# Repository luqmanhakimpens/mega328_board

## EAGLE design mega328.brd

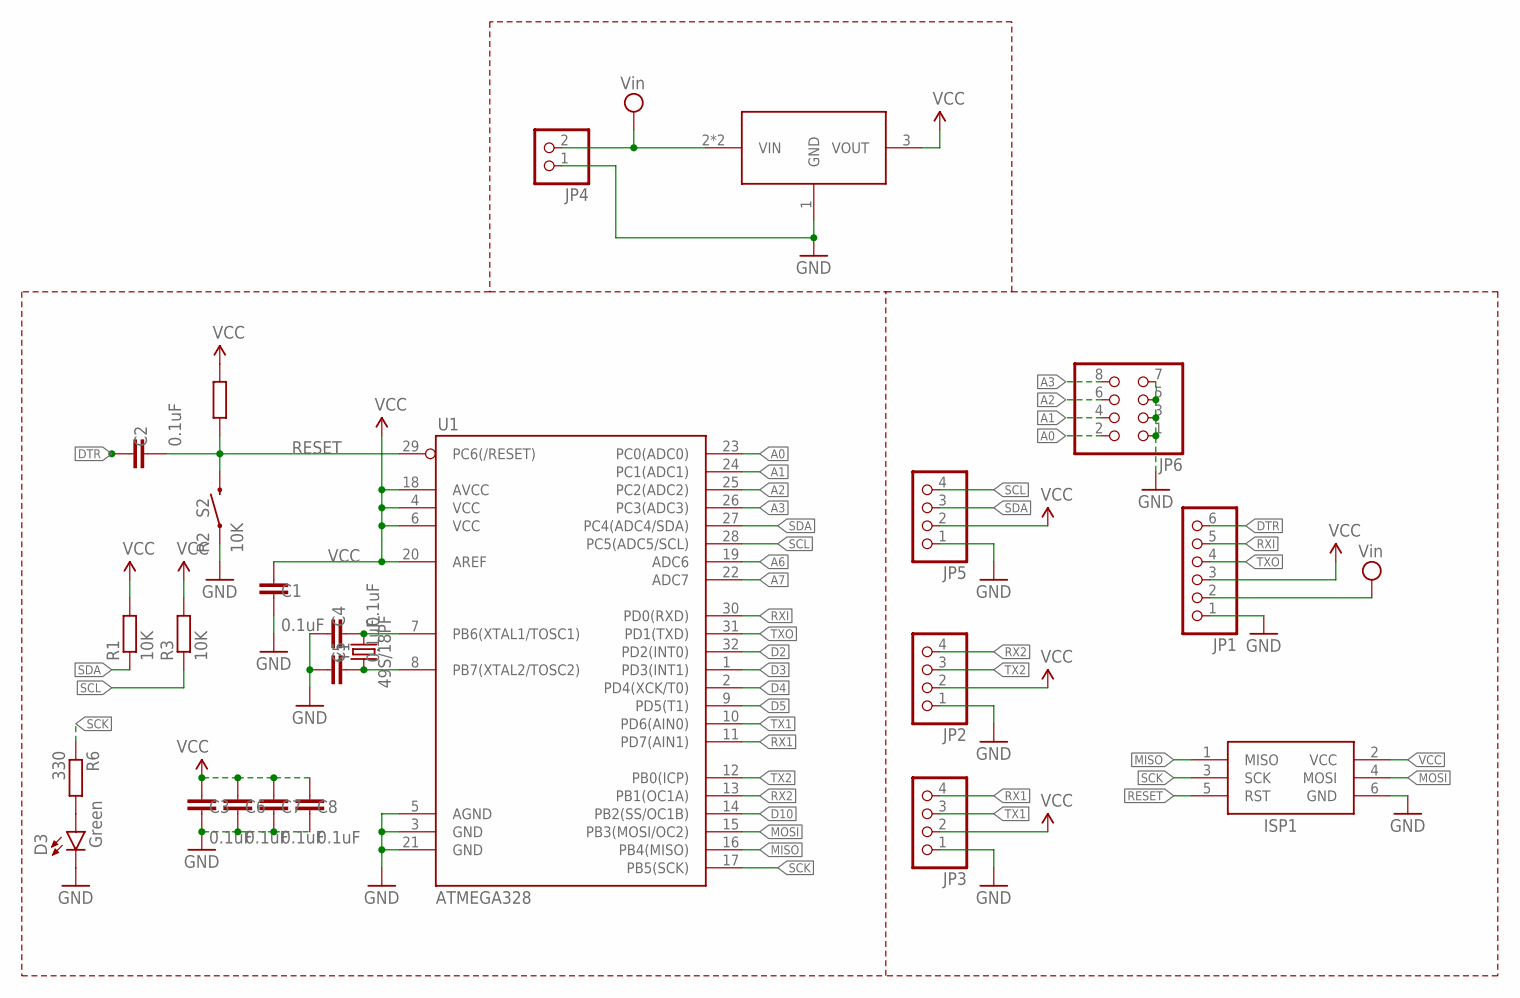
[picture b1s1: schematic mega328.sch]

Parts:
C1, C2, C3, C4, C5, C6, C7, C8: 0.1uF; C0805
D3: Green; CHIP-LED0805
ISP1: AVRISP3D; 2X03
JP1: PINHD-1X06_2.54-S; 1X06
JP2, JP3, JP5: PINHD-1X04_2.54-S; 1X04-S
JP4: PINHD-1X02_2.54-S; 1X02-S
JP6: PINHD-2X4; 2X04
R1, R2, R3: 10K; R0805
R6: 330; R0805
S2: MOMENTARY-SWITCH-SPST-PTH-6.0MM; TACTILE_SWITCH_PTH_6.0MM
U1: ATMEGA328; TQFP32-08
U$1: AIC1722A-33PXATR; SOT89
Y1: 49S/18PF; XTAL_HC49

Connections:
A0: JP6.2, U1.23 (PC0(ADC0))
A1: JP6.4, U1.24 (PC1(ADC1))
A2: JP6.6, U1.25 (PC2(ADC2))
A3: JP6.8, U1.26 (PC3(ADC3))
A6: U1.19 (ADC6)
A7: U1.22 (ADC7)
D2: U1.32 (PD2(INT0))
D3: U1.1 (PD3(INT1))
D4: U1.2 (PD4(XCK/T0))
D5: U1.9 (PD5(T1))
D10: U1.14 (PB2(SS/OC1B))
DTR: C2.2, JP1.6
GND: C1.1, C3.1, C4.2, C5.2, C6.1, C7.1, C8.1, D3.C, ISP1.6 (GND), JP1.1, JP2.1, JP3.1, JP4.1, JP5.1, JP6.1, JP6.3, JP6.5, JP6.7, S2.1, S2.2 (1), U1.3 (GND), U1.5 (AGND), U1.21 (GND), U$1.1 (GND)
MISO: ISP1.1 (MISO), U1.16 (PB4(MISO))
MOSI: ISP1.4 (MOSI), U1.15 (PB3(MOSI/OC2))
unnamed: C5.1, U1.8 (PB7(XTAL2/TOSC2)), Y1.1
unnamed: C4.1, U1.7 (PB6(XTAL1/TOSC1)), Y1.2
unnamed: D3.A, R6.2
RESET: C2.1, ISP1.5 (RST), R2.1, S2.3 (2), S2.4 (2), U1.29 (PC6(/RESET))
RX1: JP3.4, U1.11 (PD7(AIN1))
RX2: JP2.4, U1.13 (PB1(OC1A))
RXI: JP1.5, U1.30 (PD0(RXD))
SCK: ISP1.3 (SCK), R6.1, U1.17 (PB5(SCK))
SCL: JP5.4, R3.1, U1.28 (PC5(ADC5/SCL))
SDA: JP5.3, R1.1, U1.27 (PC4(ADC4/SDA))
TX1: JP3.3, U1.10 (PD6(AIN0))
TX2: JP2.3, U1.12 (PB0(ICP))
TXO: JP1.4, U1.31 (PD1(TXD))
VCC: C1.2, C3.2, C6.2, C7.2, C8.2, ISP1.2 (VCC), JP1.3, JP2.2, JP3.2, JP5.2, R1.2, R2.2, R3.2, U1.4 (VCC), U1.6 (VCC), U1.18 (AVCC), U1.20 (AREF), U$1.3 (VOUT)
VIN: JP1.2, JP4.2, U$1.2 (VIN), U$1.2@1 (VIN)

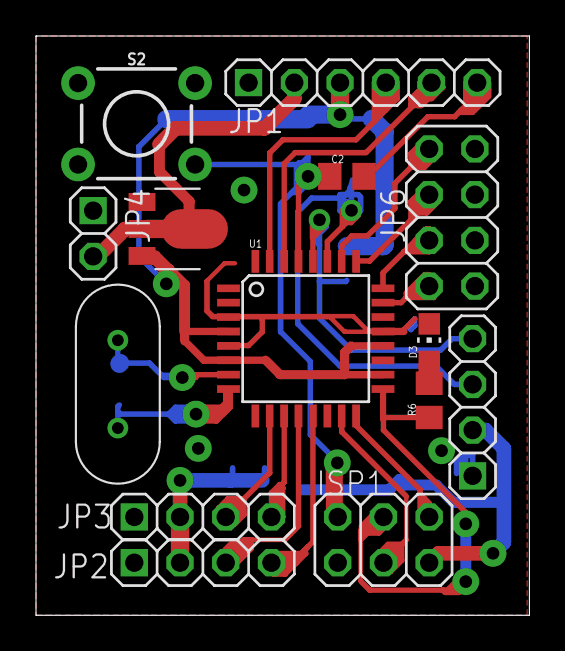
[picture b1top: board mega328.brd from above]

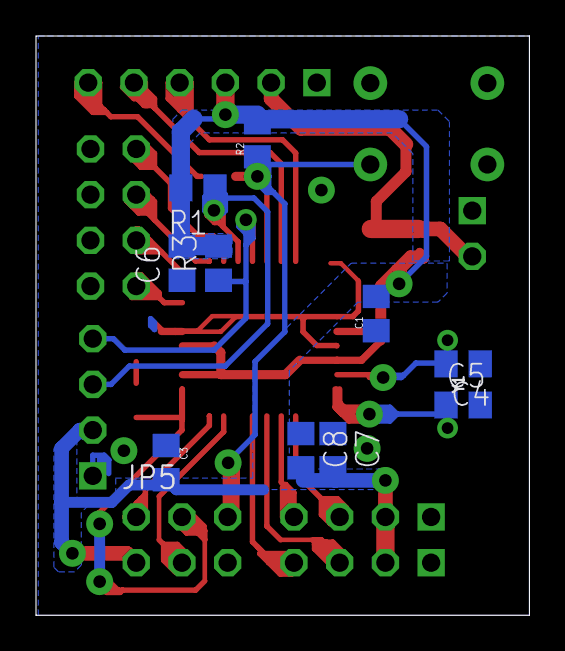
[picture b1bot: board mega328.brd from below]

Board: 2 copper layers, 27.4 x 32.2 mm, 24 parts (10 on the bottom side), 23 nets.

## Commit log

2020-05-08 init

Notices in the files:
parts and their libraries:
SparkFun-Switches-edit: Licensing: Creative Commons ShareAlike 4.0 International - https://creativecommons.org/licenses/by-sa/4.0
